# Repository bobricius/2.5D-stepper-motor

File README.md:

It is compatible with standard stepper motor diver, cnc or GRBL shield, 
direct replacement of X-Y stepper motors. 

With flexible boards you can partial move in Z axe :) if you warp board. 
Magnet is moved only in horizontal X-Y space. It can push small object, I have no way 
now how to pick and place object or I have no communication and feedback from robot. 

Feedback is possible with camera or hall sensors under board, also there is way 
to communicate with bot over NFC/RFID with coil under board... untested now 

you can move only one magnet, more magnets move paralel, but you can 
divide moving space to zones and use more robots ... etc parking zones if you have more 
magneboots with different tools 

My latest design use 0.6mm board but this is very fat, 
bottom trackers are weak compared to top trackers 

I have plan make only tracking part from flex and controller as normal 1.6mm board 

5x5mm moving magnets 4pcs x 2mm magnet .

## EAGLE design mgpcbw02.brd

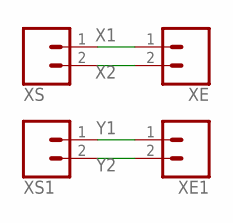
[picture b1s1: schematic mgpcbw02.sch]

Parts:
XE, XE1: CONN_021X02_NO_SILK; 1X02_NO_SILK
XS, XS1: CONN_021X02_NO_SILK; 1X02_NO_SILK

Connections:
X1: XE.1, XS.1
X2: XE.2, XS.2
Y1: XE1.1, XS1.1
Y2: XE1.2, XS1.2

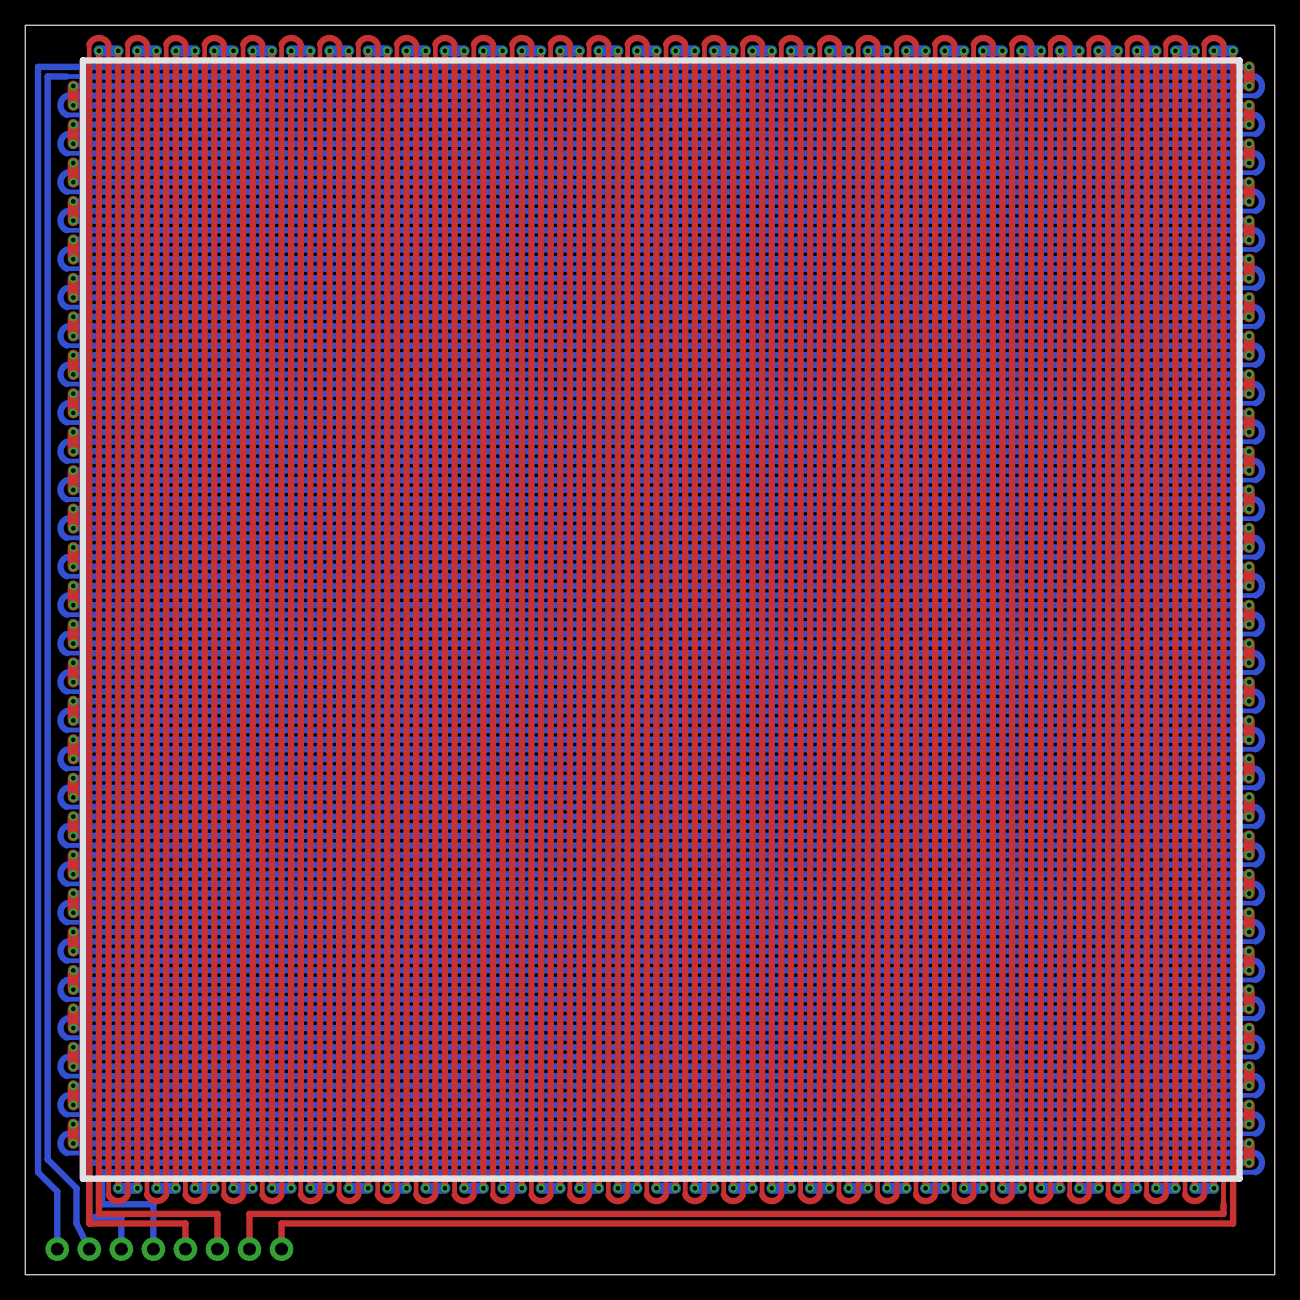
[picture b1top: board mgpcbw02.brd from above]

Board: 2 copper layers, 99.1 x 99.1 mm, 4 parts (0 on the bottom side), 4 nets.

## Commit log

2019-04-25 uploaded design files

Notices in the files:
parts and their libraries:
SparkFun-Connectors: Licensing: Creative Commons ShareAlike 4.0 International - https://creativecommons.org/licenses/by-sa/4.0
